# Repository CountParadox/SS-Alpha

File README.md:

# SS-Alpha
Sendspin Alpha Audio Receiver open source aspects.

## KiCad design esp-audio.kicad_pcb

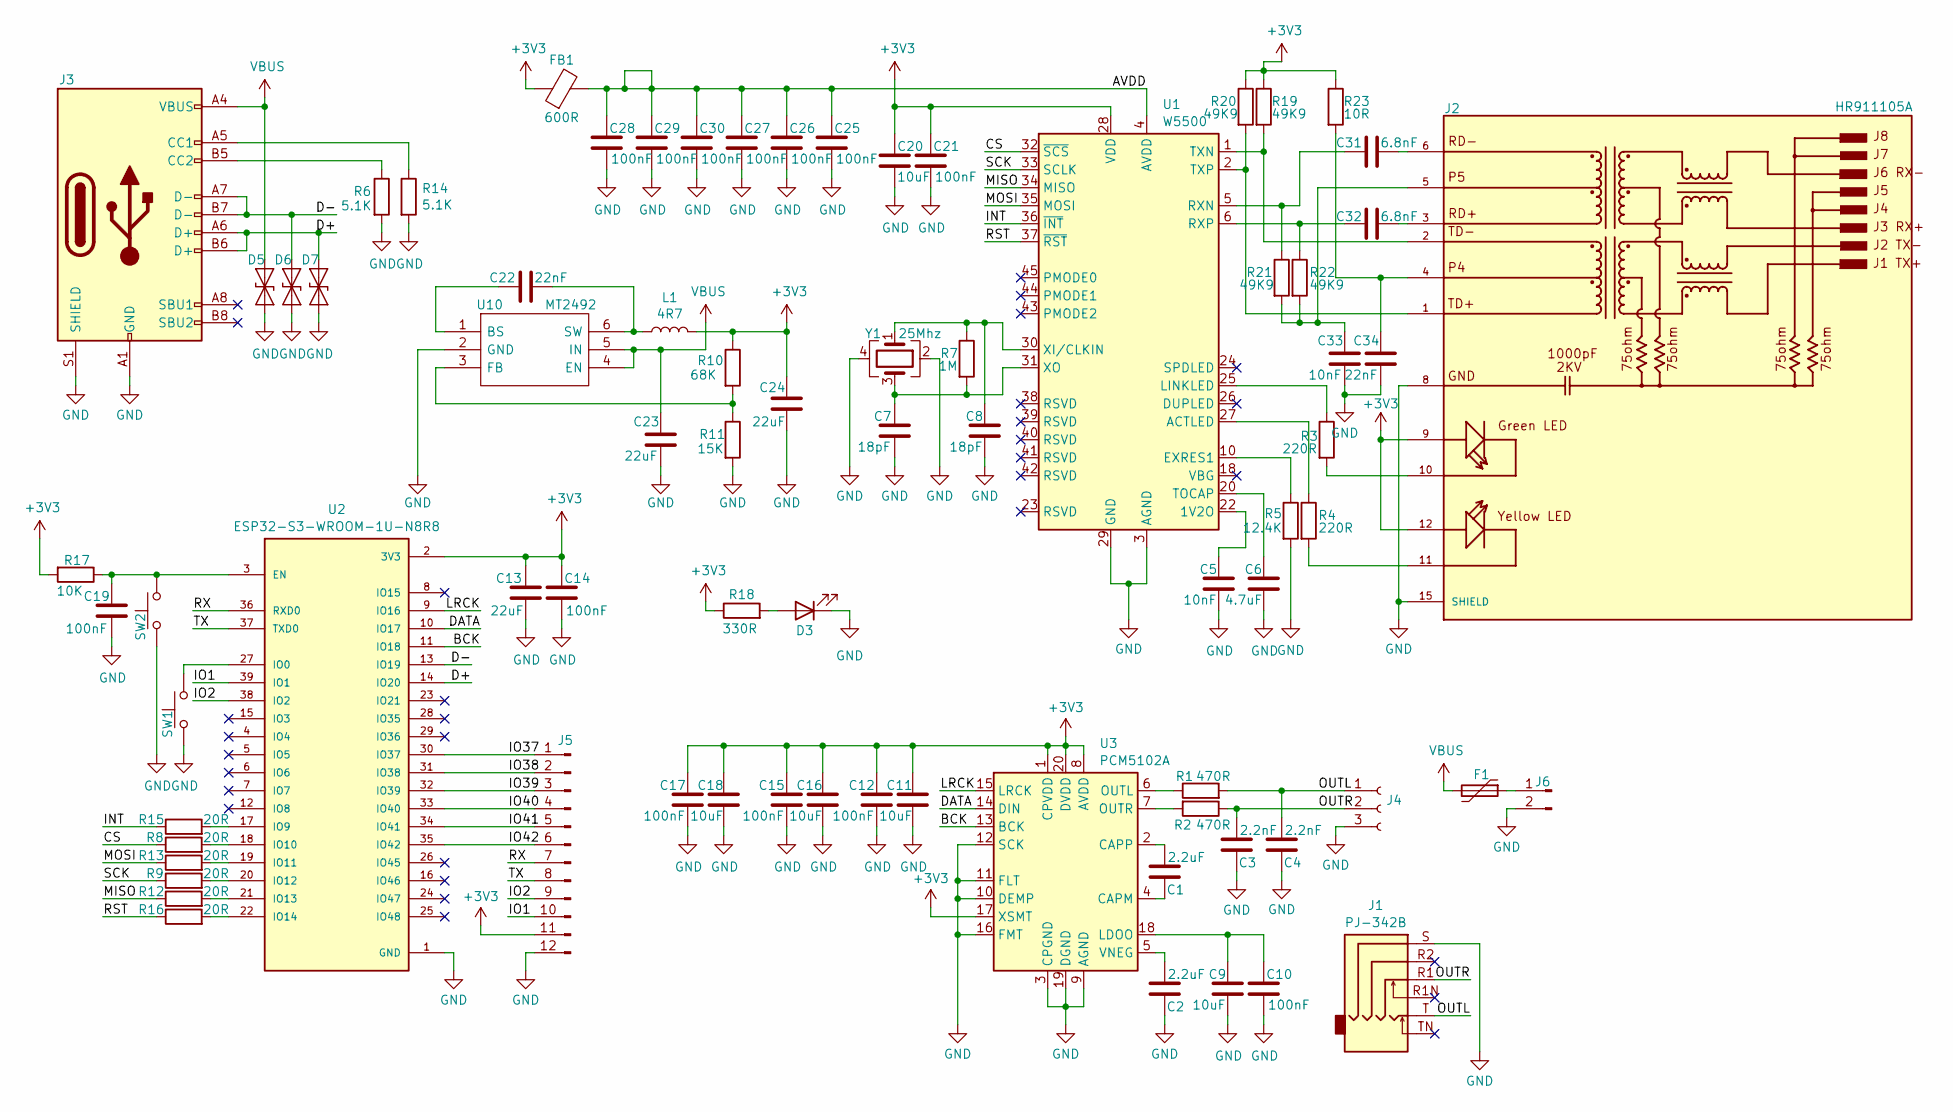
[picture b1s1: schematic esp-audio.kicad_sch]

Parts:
C1, C2: 2.2uF; C_0603_1608Metric; LCSC C23630
C3, C4: 2.2nF; C_0603_1608Metric; LCSC C1604
C5, C33: 10nF; C_0603_1608Metric; LCSC C57112
C6: 4.7uF; C_0603_1608Metric; LCSC C19666
C7, C8: 18pF; C_0603_1608Metric; LCSC C1647
C9, C11, C16, C18, C20: 10uF; C_0603_1608Metric; LCSC C96446
C10, C12, C14, C15, C17, C19, C21, C25, C26, C27, C28, C29, C30: 100nF; C_0603_1608Metric; LCSC C14663
C13, C23: 22uF; C_0603_1608Metric; LCSC C59461
C22, C34: 22nF; C_0603_1608Metric; LCSC C21122
C24: 22uF; C_0603_1608Metric; LCSC C2762594
C31, C32: 6.8nF; C_0603_1608Metric; LCSC C1631
D3: LED; LED_0603_1608Metric; LCSC C2286
D5, D6, D7: ESD5B5; D_SOD-523; LCSC C93623
F1: 3A 12V; Fuse_1206_3216Metric; LCSC C516068
FB1: 600R; L_0603_1608Metric; LCSC C1002
J1: PJ-342B; LCSC C668606
J2: HR911105A; HANRUN_HR911105A; LCSC C12074
J3: USB_C_Receptacle_USB2.0; USB-C_SMD-TYPE-C-31-M-12; LCSC C167321
J4: Conn_01x03_Socket; PhoenixContact_MC_1,5_3-G-3.5_1x03_P3.50mm_Horizontal; LCSC C5188296
J5: Conn_01x12_Pin; PinHeader_2x06_P2.54mm_Vertical; LCSC C7501277
J6: Conn_01x02_Pin; PinHeader_1x02_P2.54mm_Vertical
L1: 4R7; L_0603_1608Metric; LCSC C394952
R1, R2: 470R; R_0603_1608Metric; LCSC C23179
R3, R4: 220R; R_0603_1608Metric; LCSC C22962
R5: 12.4K; R_0603_1608Metric; LCSC C22865
R6, R14: 5.1K; R_0603_1608Metric; LCSC C14677
R7: 1M; R_0603_1608Metric; LCSC C22935
R8, R9, R12, R13, R15, R16: 20R; R_0603_1608Metric; LCSC C22950
R10: 68K; R_0603_1608Metric; LCSC C23231
R11: 15K; R_0603_1608Metric; LCSC C22809
R17: 10K; R_0603_1608Metric; LCSC C25804
R18: 330R; R_0603_1608Metric; LCSC C23138
R19, R20, R21, R22: 49K9; R_0603_1608Metric; LCSC C23184
R23: 10R; R_0603_1608Metric; LCSC C22859
SW1, SW2: SW_Push; TS1088R02026; LCSC C455280
U1: W5500; LQFP-48_7x7mm_P0.5mm; LCSC C32843
U2: ESP32-S3-WROOM-1U-N8R8; XCVR_ESP32-S3-WROOM-1U-N8R8; PARTREV v1.1; LCSC C2980300
U3: PCM5102A; TSSOP-20_4.4x6.5mm_P0.65mm; LCSC C107671
U10: MT2492; SOT95P280X145-6N; LCSC C89358
Y1: 25Mhz; Crystal_SMD_3225-4Pin_3.2x2.5mm; LCSC C9006

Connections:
+3V3: C11.1, C12.1, C13.1, C14.1, C15.1, C16.1, C17.1, C18.1, C20.1, C21.1, C24.1, FB1.1, J2.9, J2.12, J5.11, L1.2, R10.1, R17.2, R18.1, R19.1, R20.1, R23.1, U1.28 (VDD), U2.2 (3V3), U3.1 (CPVDD), U3.8 (AVDD), U3.17 (XSMT), U3.20 (DVDD)
/AVDD: C25.1, C26.1, C27.1, C28.1, C29.1, C30.1, FB1.2, U1.4 (AVDD), U1.8 (AVDD), U1.11 (AVDD), U1.15 (AVDD), U1.17 (AVDD), U1.21 (AVDD)
/BCK: U2.11 (IO18), U3.13 (BCK)
/CS: R8.1, U1.32 (~SCS)
/D+: D7.1 (A1), J3.A6 (D+), J3.B6 (D+), U2.14 (IO20)
/D-: D6.1 (A1), J3.A7 (D-), J3.B7 (D-), U2.13 (IO19)
/DATA: U2.10 (IO17), U3.14 (DIN)
/INT: R15.1, U1.36 (~INT)
/IO1: J5.10, U2.39 (IO1)
/IO2: J5.9, U2.38 (IO2)
/IO37: J5.1, U2.30 (IO37)
/IO38: J5.2, U2.31 (IO38)
/IO39: J5.3, U2.32 (IO39)
/IO40: J5.4, U2.33 (IO40)
/IO41: J5.5, U2.34 (IO41)
/IO42: J5.6, U2.35 (IO42)
/LRCK: U2.9 (IO16), U3.15 (LRCK)
/MISO: R12.1, U1.34 (MISO)
/MOSI: R13.1, U1.35 (MOSI)
/OUTL: C4.2, J1.T, J4.1, R1.2; also elsewhere on the board
/OUTR: C3.2, J1.R1, J4.2, R2.1; also elsewhere on the board
/RST: R16.1, U1.37 (~RST)
/RX: J5.7, U2.36 (RXD0)
/SCK: R9.1, U1.33 (SCLK)
/TX: J5.8, U2.37 (TXD0)
GND: C2.1, C3.1, C4.1, C5.2, C6.2, C7.2, C8.2, C9.2, C10.2, C11.2, C12.2, C13.2, C14.2, C15.2, C16.2, C17.2, C18.2, C19.2, C20.2, C21.2, C23.2, C24.2, C25.2, C26.2, C27.2, C28.2, C29.2, C30.2, C33.2, C34.2, D3.1 (K), D5.2 (A2), D6.2 (A2), D7.2 (A2), J1.S, J2.8, J2.15 (SHIELD), J2.16 (SHIELD), J3.A1 (GND), J3.A12 (GND), J3.B1 (GND), J3.B12 (GND), J3.S1 (SHIELD), J4.3, J5.12, J6.2, R5.2, R6.2, R11.2, R14.2, SW1.1, SW2.1, U1.3 (AGND), U1.9 (AGND), U1.14 (AGND), U1.16 (AGND), U1.19 (AGND), U1.29 (GND), U1.48 (AGND), U2.1 (GND), U2.40 (GND), U2.41 (GND), U3.3 (CPGND), U3.9 (AGND), U3.10 (DEMP), U3.11 (FLT), U3.12 (SCK), U3.16 (FMT), U3.19 (DGND), U10.2 (GND), Y1.2, Y1.4
unnamed: C31.2, J2.6
unnamed: C32.2, J2.3
unnamed: C33.1, J2.5, R21.2, R22.2
unnamed: C34.1, J2.4, R23.2
unnamed: D3.2 (A), R18.2
unnamed: J2.10, R3.2
unnamed: J2.11, R4.2
unnamed: J3.A5 (CC1), R14.1
unnamed: J3.B5 (CC2), R6.1
unnamed: F1.1, J6.1
unnamed: C5.1, U1.22 (1V2O)
unnamed: R4.1, U1.27 (ACTLED)
unnamed: R5.1, U1.10 (EXRES1)
unnamed: R3.1, U1.25 (LINKLED)
unnamed: C31.1, R21.1, U1.5 (RXN)
unnamed: C32.1, R22.1, U1.6 (RXP)
unnamed: C6.1, U1.20 (TOCAP)
unnamed: J2.2, R19.2, U1.1 (TXN)
unnamed: J2.1, R20.2, U1.2 (TXP)
unnamed: C8.1, R7.1, U1.30 (XI/CLKIN), Y1.1
unnamed: C7.1, R7.2, U1.31 (XO), Y1.3
unnamed: C19.1, R17.1, SW2.2, U2.3 (EN)
unnamed: SW1.2, U2.27 (IO0)
unnamed: R15.2, U2.17 (IO9)
unnamed: R8.2, U2.18 (IO10)
unnamed: R13.2, U2.19 (IO11)
unnamed: R9.2, U2.20 (IO12)
unnamed: R12.2, U2.21 (IO13)
unnamed: R16.2, U2.22 (IO14)
unnamed: C1.1, U3.4 (CAPM)
unnamed: C1.2, U3.2 (CAPP)
unnamed: C9.1, C10.1, U3.18 (LDOO)
unnamed: R1.1, U3.6 (OUTL)
unnamed: R2.2, U3.7 (OUTR)
unnamed: C2.2, U3.5 (VNEG)
unnamed: C22.2, U10.1 (BS)
unnamed: R10.2, R11.1, U10.3 (FB)
unnamed: C22.1, L1.1, U10.6 (SW)
VBUS: C23.1, D5.1 (A1), F1.2, J3.A4 (VBUS), J3.A9 (VBUS), J3.B4 (VBUS), J3.B9 (VBUS), U10.4 (EN), U10.5 (IN)

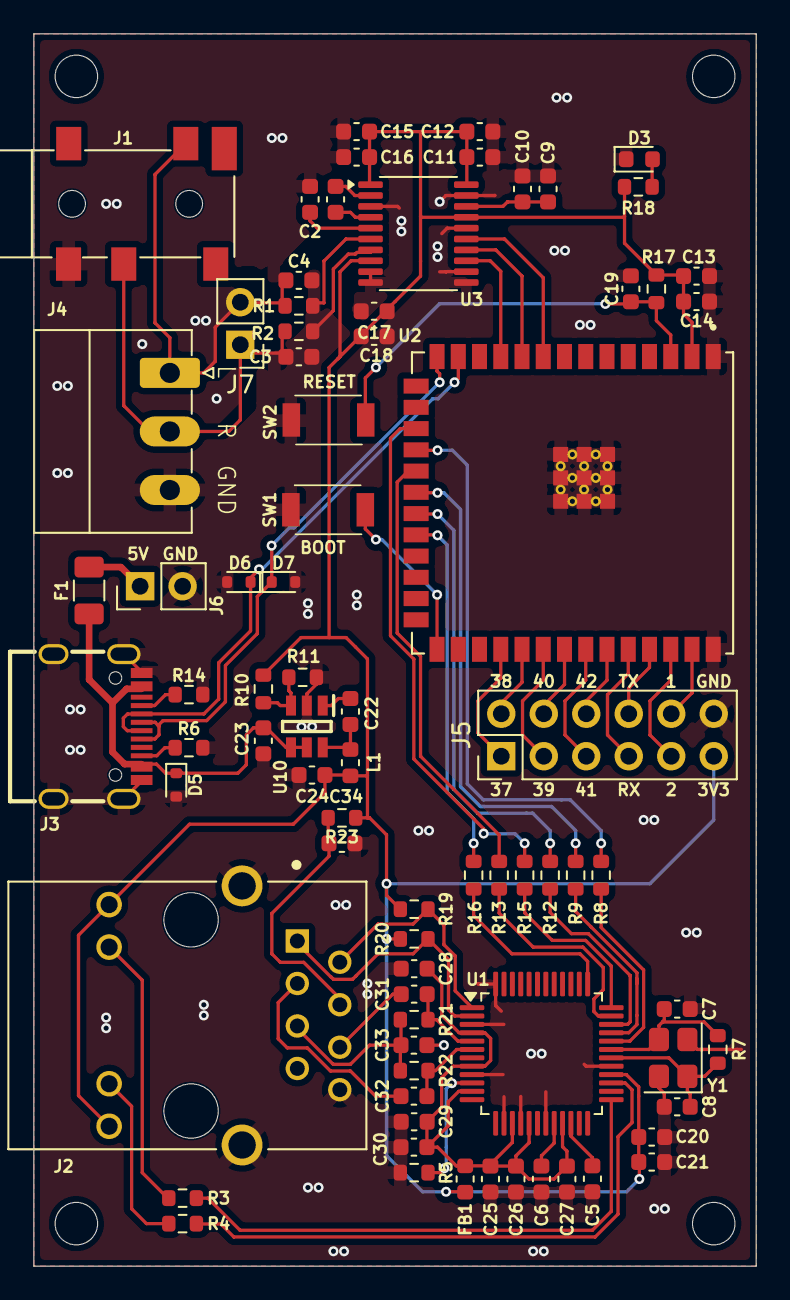
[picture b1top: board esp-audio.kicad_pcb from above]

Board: 2 copper layers, 43.2 x 73.7 mm, 78 parts (0 on the bottom side), 65 nets.

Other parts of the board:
J7: <= MONO_MIX; PinHeader_1x02_P2.54mm_Vertical

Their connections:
/OUTL: J7.2; also elsewhere on the board
/OUTR: J7.1; also elsewhere on the board

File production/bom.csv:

Designator,Footprint,Quantity,Value,LCSC Part #
"C1, C2",0603,2,2.2uF,C23630
"C10, C12, C14, C15, C17, C19, C21, C25, C26, C27, C28, C29, C30",0603,13,100nF,C14663
"C11, C16, C18, C20, C9",0603,5,10uF,C96446
"C13, C23",0603,2,22uF,C59461
"C22, C34",0603,2,22nF,C21122
C24,0603,1,22uF,C2762594
"C3, C4",0603,2,2.2nF,C1604
"C31, C32",0603,2,6.8nF,C1631
"C33, C5",0603,2,10nF,C57112
C6,0603,1,4.7uF,C19666
"C7, C8",0603,2,18pF,C1647
D3,0603,1,LED,C2286
"D5, D6, D7",D_SOD-523,3,ESD5B5,C93623
F1,1206,1,3A 12V,C516068
FB1,0603,1,600R,C1002
J1,PJ-342B,1,PJ-342B,C668606
J2,HANRUN_HR911105A,1,HR911105A,C12074
J3,USB-C_SMD-TYPE-C-31-M-12,1,USB_C_Receptacle_USB2.0,C167321
J4,"PhoenixContact_MC_1,5_3-G-3.5_1x03_P3.50mm_Horizontal",1,Conn_01x03_Socket,C5188296
J5,PinHeader_2x06_P2.54mm_Vertical,1,Conn_01x12_Pin,C7501277
L1,0603,1,4R7,C394952
"R1, R2",0603,2,470R,C23179
R10,0603,1,68K,C23231
R11,0603,1,15K,C22809
"R12, R13, R15, R16, R8, R9",0603,6,20R,C22950
"R14, R6",0603,2,5.1K,C14677
R17,0603,1,10K,C25804
R18,0603,1,330R,C23138
"R19, R20, R21, R22",0603,4,49K9,C23184
R23,0603,1,10R,C22859
"R3, R4",0603,2,220R,C22962
R5,0603,1,12.4K,C22865
R7,0603,1,1M,C22935
"SW1, SW2",TS1088R02026,2,SW_Push,C455280
U1,LQFP-48_7x7mm_P0.5mm,1,W5500,C32843
U10,SOT95P280X145-6N,1,MT2492,C89358
U2,XCVR_ESP32-S3-WROOM-1U-N8R8,1,ESP32-S3-WROOM-1U-N8R8,C2980300
U3,TSSOP-20_4.4x6.5mm_P0.65mm,1,PCM5102A,C107671
Y1,Crystal_SMD_3225-4Pin_3.2x2.5mm,1,25Mhz,C9006

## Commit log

2026-03-01 initial
2026-05-14 Create configuration for Sendspin Alpha device
    Add configuration for Sendspin Alpha device with audio and LED control.
2026-05-14 added blue pulse when playing
2026-05-23 fix USB D+/D-, caps, add power pins
2026-05-23 Add hardware/dummy.txt
2026-05-23 kicad 10
2026-05-23 added mono mix pin header (jumper pins to mix L and R channels)
2026-05-23 fixed save
